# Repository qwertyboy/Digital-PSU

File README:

Digital PSU

This originally started life as the revision B EEVBlog power supply project, but I have made several changes to my version of the design. The first revision of ym design was pretty much a carbon copy of the EEVBlog design, but removed the USB jack and the micro current section. The board was designed with all through-hole components, except for the components that only come in SMD packages, and as a result, was larger and more expensive to produce. The new version, however, only uses through-hole versions of the DAC, ADC, op-amps, the LT3080, and a couple filter capacitors. Instead of using an atmega328 now, it uses an Xmega A4, both for speed and for I/O count. Also changed are the elimination of the push-buttons and MCP23008 I/O expanders.

Key Features:
	-Xmega A4 simplifies design by eliminating need for I/O expansion
	-LT3080 as main output regulator
	-MCP4922 digital-to-analog converter
	-MCP3204 analog-to-digital converter
	-MAX4080F for current sensing
	-Easily readible OLED display
	-Intuitive menu system for set-up and calibration

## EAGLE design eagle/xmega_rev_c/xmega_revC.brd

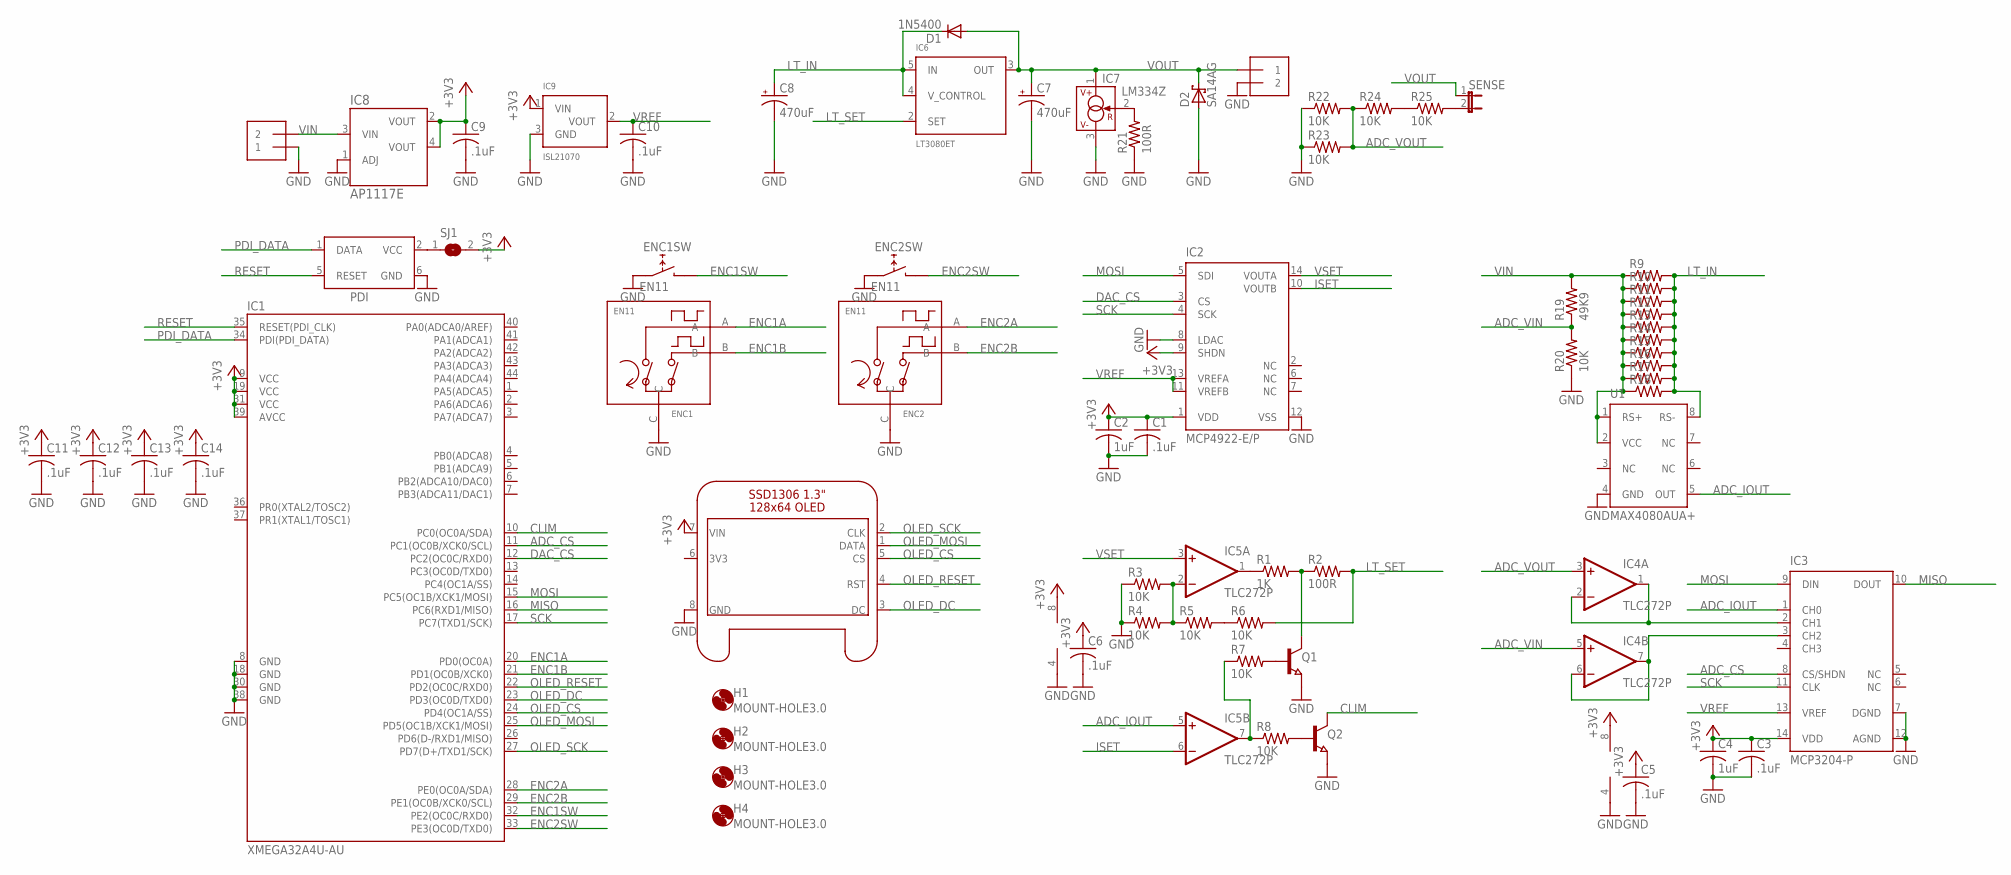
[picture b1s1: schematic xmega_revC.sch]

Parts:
C1, C3, C5, C6, C9, C10: .1uF; C050-024X044
C2, C4: 1uF; C050-024X044
C7, C8: 470uF; E5-10,5
C11, C12, C13, C14: .1uF; C0805K
D1: 1N5400; DO201-15
D2: SA14AG; DO41-7
ENC1, ENC2: EN11; EN11-VS*
H1, H2, H3, H4: MOUNT-HOLE3.0; 3,0
IC1: XMEGA32A4U-AU; TQFP44
IC2: MCP4922-E/P; DIL14
IC3: MCP3204-P; DIL14
IC4, IC5: TLC272P; DIL08
IC6: LT3080ET; TO220-51
IC7: LM334Z; TO92
IC8: AP1117E; SOT223-3
IC9: ISL21070; SOT-23
OLED1: 128X64_OLED
OUT: 1X2-3.5MM
PDI: XMEGAPDI; AVRISP
Q1, Q2: NPN-TRANSISTOR_SOT23; SOT23
R1: 1K; R0805
R2, R21: 100R; R0805
R3, R4, R5, R6, R7, R8, R20, R22, R23, R24, R25: 10K; R0805
R9, R10, R11, R12, R13, R14, R15, R16, R17, R18: R-US_0207/10; 0207/10
R19: 49K9; R0805
SENSE: JP1E; JP1
SJ1: SJ
U1: MAX4080AUA+; SO08
VIN: 1X2-3.5MM

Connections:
3V3: OLED1.6 (3V3)
+3V3: C1.1, C2.1, C3.1, C4.1, C5.1, C6.1, C9.1, C11.1, C12.1, C13.1, C14.1, IC1.9 (VCC), IC1.19 (VCC), IC1.31 (VCC), IC1.39 (AVCC), IC2.1 (VDD), IC2.9 (SHDN), IC3.14 (VDD), IC4.8 (V+), IC5.8 (V+), IC8.2 (VOUT), IC8.4 (VOUT), IC9.1 (VIN), OLED1.7 (VIN), SJ1.2
ADC_CS: IC1.11 (PC1(OC0B/XCK0/SCL)), IC3.8 (CS/SHDN)
ADC_IOUT: IC3.1 (CH0), IC5.5 (+IN), U1.5 (OUT)
ADC_VIN: IC4.5 (+IN), R19.1, R20.2
ADC_VOUT: IC4.3 (+IN), R22.2, R23.2, R24.1
CLIM: IC1.10 (PC0(OC0A/SDA)), Q2.3 (C)
DAC_CS: IC1.12 (PC2(OC0C/RXD0)), IC2.3 (CS)
ENC1A: ENC1.A, IC1.20 (PD0(OC0A))
ENC1B: ENC1.B, IC1.21 (PD1(OC0B/XCK0))
ENC1SW: ENC1.E, IC1.32 (PE2(OC0C/RXD0))
ENC2A: ENC2.A, IC1.28 (PE0(OC0A/SDA))
ENC2B: ENC2.B, IC1.29 (PE1(OC0B/XCK0/SCL))
ENC2SW: ENC2.E, IC1.33 (PE3(OC0D/TXD0))
GND: C1.2, C2.2, C3.2, C4.2, C5.2, C6.2, C7.-, C8.-, C9.2, C10.2, C11.2, C12.2, C13.2, C14.2, D2.A, ENC1.C, ENC1.D, ENC2.C, ENC2.D, IC1.8 (GND), IC1.18 (GND), IC1.30 (GND), IC1.38 (GND), IC2.8 (LDAC), IC2.12 (VSS), IC3.7 (DGND), IC3.12 (AGND), IC4.4 (V-), IC5.4 (V-), IC7.3 (V-), IC8.1 (ADJ), IC9.3 (GND), OLED1.8 (GND), OUT.2, PDI.6 (GND), Q1.2 (E), Q2.2 (E), R3.1, R4.1, R20.1, R21.1, R22.1, R23.1, U1.4 (GND), VIN.1
ISET: IC2.10 (VOUTB), IC5.6 (-IN)
LT_IN: C8.+, D1.C, IC6.4 (V_CONTROL), IC6.5 (IN), R9.2, R10.2, R11.2, R12.2, R13.2, R14.2, R15.2, R16.2, R17.2, R18.2, U1.8 (RS-)
LT_SET: IC6.2 (SET), R2.2, R6.2
MISO: IC1.16 (PC6(RXD1/MISO)), IC3.10 (DOUT)
MOSI: IC1.15 (PC5(OC1B/XCK1/MOSI)), IC2.5 (SDI), IC3.9 (DIN)
unnamed: IC3.2 (CH1), IC4.1 (OUT), IC4.2 (-IN)
unnamed: IC3.3 (CH2), IC4.6 (-IN), IC4.7 (OUT)
unnamed: IC5.1 (OUT), R1.1
unnamed: Q1.3 (C), R1.2, R2.1
unnamed: IC5.2 (-IN), R3.2, R4.2, R5.1
unnamed: R5.2, R6.1
unnamed: Q1.1 (B), R7.2
unnamed: IC5.7 (OUT), R7.1, R8.1
unnamed: Q2.1 (B), R8.2
unnamed: R25.2, SENSE.2
unnamed: PDI.2 (VCC), SJ1.1
unnamed: IC7.2 (R), R21.2
unnamed: R24.2, R25.1
OLED_CS: IC1.24 (PD4(OC1A/SS)), OLED1.5 (CS)
OLED_DC: IC1.23 (PD3(OC0D/TXD0)), OLED1.3 (DC)
OLED_MOSI: IC1.25 (PD5(OC1B/XCK1/MOSI)), OLED1.1 (DATA)
OLED_RESET: IC1.22 (PD2(OC0C/RXD0)), OLED1.4 (RST)
OLED_SCK: IC1.27 (PD7(D+/TXD1/SCK)), OLED1.2 (CLK)
PDI_DATA: IC1.34 (PDI(PDI_DATA)), PDI.1 (DATA)
RESET: IC1.35 (RESET(PDI_CLK)), PDI.5 (RESET)
SCK: IC1.17 (PC7(TXD1/SCK)), IC2.4 (SCK), IC3.11 (CLK)
VIN: IC8.3 (VIN), R9.1, R10.1, R11.1, R12.1, R13.1, R14.1, R15.1, R16.1, R17.1, R18.1, R19.2, U1.1 (RS+), U1.2 (VCC), VIN.2
VOUT: C7.+, D1.A, D2.C, IC6.3 (OUT), IC7.1 (V+), OUT.1, SENSE.1
VREF: C10.1, IC2.11 (VREFB), IC2.13 (VREFA), IC3.13 (VREF), IC9.2 (VOUT)
VSET: IC2.14 (VOUTA), IC5.3 (+IN)

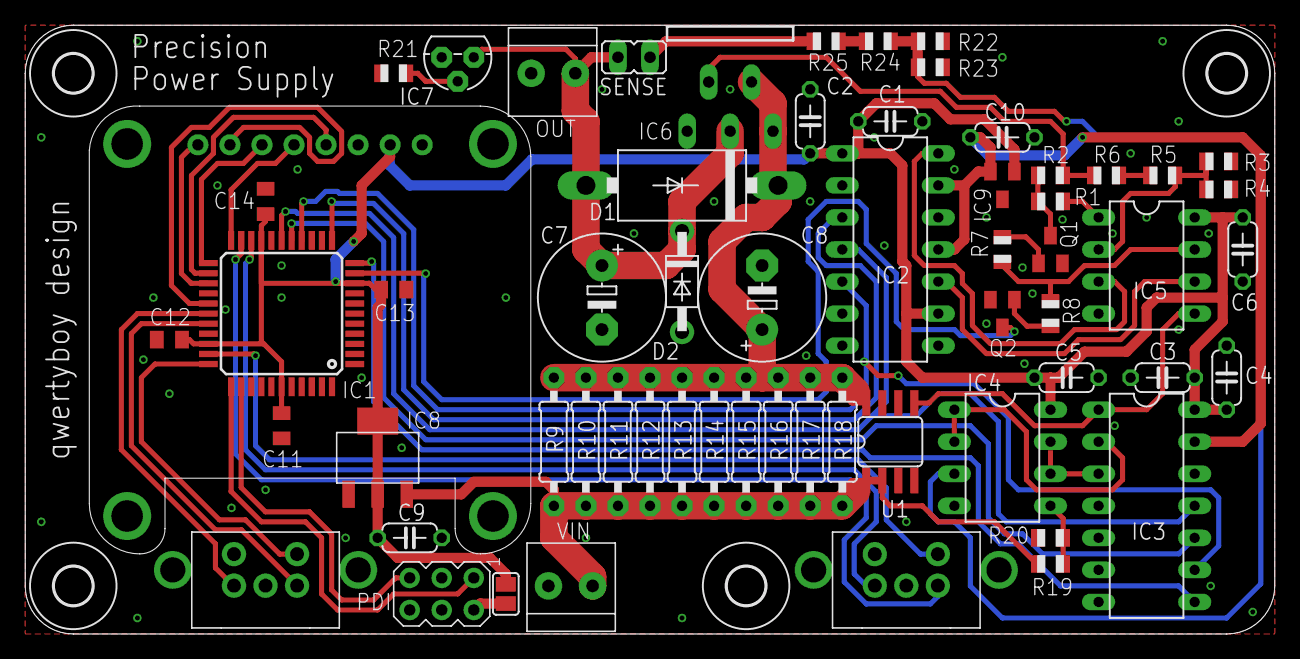
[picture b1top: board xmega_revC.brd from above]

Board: 2 copper layers, 99.1 x 48.3 mm, 65 parts (0 on the bottom side), 44 nets.

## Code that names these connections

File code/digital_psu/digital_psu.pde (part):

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
//Define some constants
//The first four here are on mcp_internal
#define DAC_CS 1
#define ADC_CS 0
#define RANGE 2  //Range selection for rev.B boards, not used anyway
#define LCD_RESET 3

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#define MENUBUTTON 0

//Rotary encoder pins
#define ENC1A 2
#define ENC1B 4
#define ENC2A 3
#define ENC2B 7

//These are the counts for the rotary encoders. They are volatile because they will be modified
//in an interrupt and we don't want the compiler to try and optimise these
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//Define some ADC constants
#define IOUT200 0
#define IOUT 1
#define VOUT 2
#define VIN 3
float VOLTAGE_PRINT_DIVISOR = 333.889816;  //This is to output the correct value after voltage
                                           //divider and ADC. Only to be used for VIN
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  mcp_internal.digitalWrite(LCD_RESET, HIGH);

  //Bring CS lines high to ignore stray data
  mcp_internal.pinMode(DAC_CS, OUTPUT);
  mcp_internal.pinMode(ADC_CS, OUTPUT);
  mcp_internal.digitalWrite(DAC_CS, HIGH);
  mcp_internal.digitalWrite(ADC_CS, HIGH);

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  pinMode(ADC_DATA, INPUT);

  //Set up rotary encoder pins
  pinMode(ENC1A, INPUT);
  pinMode(ENC1B, INPUT);
  pinMode(ENC2A, INPUT);
  pinMode(ENC2B, INPUT);
  digitalWrite(ENC1A, HIGH);
  digitalWrite(ENC1B, HIGH);
  digitalWrite(ENC2A, HIGH);
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
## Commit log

2012-05-11 First commit. Added EAGLE schematic and layout files
2012-05-11 Added Arduino code. For Arduino version < 1
2012-05-13 Now displaying voltage output
2012-06-20 Started work on a menu system
2012-06-20 Shortened readButtons() routine
2012-06-20 Got menu set up correctly. Added _very_ touchy button navigation.
2012-06-20 Renamed some constants and variables; hopefully didn't break anything
2012-06-20 Added the libraried used for the project. See the README's in each folder for the license
2012-06-20 Commented the code more
2012-06-21 BACKUP. I added a function to detect 4 different states on one button.
2012-11-04 Updated readme for new version
2012-12-08 Added schematic and board for the newest revision, code is in progress
2012-12-08 Removed renamed files
2012-12-08 Fixing folder names. I need to get better at this ;)
